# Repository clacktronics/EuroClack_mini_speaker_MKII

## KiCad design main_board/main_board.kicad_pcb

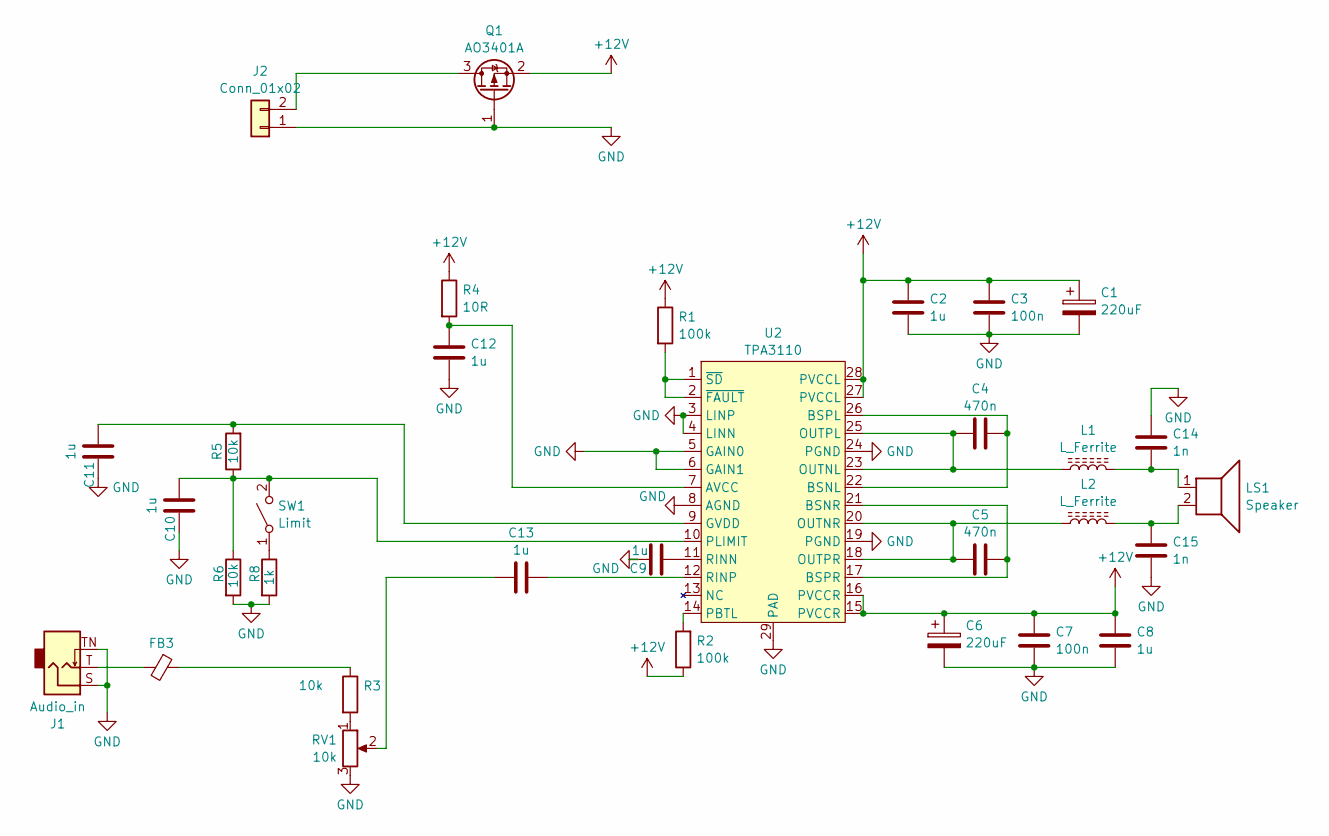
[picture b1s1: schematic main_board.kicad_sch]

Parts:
C1, C6: 220uF; CP_Elec_6.3x5.4; LCSC C2977551
C2, C8, C9, C10, C11, C12, C13: 1u; C_0805_2012Metric; LCSC C28323
C3, C7: 100n; C_0805_2012Metric; LCSC C28233
C4, C5: 470n; C_0805_2012Metric; LCSC C13967
C14, C15: 1n; C_0805_2012Metric; LCSC C46653
FB3: FerriteBead_Small; R_0603_1608Metric; LCSC C1002
J1: Audio_in; Jack_3.5mm_QingPu_WQP-PJ398SM_Vertical
J2: Conn_01x02; PinHeader_1x02_P2.54mm_Vertical
L1, L2: L_Ferrite; IND-SMD_L7.5-W7.5; LCSC C58313
LS1: Speaker; PinHeader_1x02_P2.54mm_Vertical
Q1: AO3401A; SOT-23-3; LCSC C15127
R1, R2: 100k; R_0603_1608Metric; LCSC C25803
R3, R5, R6: 10k; R_0603_1608Metric; LCSC C25804
R4: 10R; R_0805_2012Metric; LCSC C17415
R8: 1k; R_0603_1608Metric; LCSC C21190
RV1: 10k; POT_TH_Alps_RK09K_Single_Vertical
SW1: Limit; SW-SMD_SK-3293S; LCSC C466006
U2: TPA3110; HTSSOP-28-1EP_4.4x9.7mm_P0.65mm_EP2.85x5.4mm_ThermalVias; LCSC C30132

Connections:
+12V: C1.1, C2.1, C3.1, C6.1, C7.1, C8.1, Q1.2 (S), R1.1, R2.1, R4.1, U2.15 (PVCCR), U2.16 (PVCCR), U2.27 (PVCCL), U2.28 (PVCCL)
GND: C1.2, C2.2, C3.2, C6.2, C7.2, C8.2, C9.1, C10.1, C11.1, C12.1, C14.1, C15.2, J1.S, J1.TN, J2.1, Q1.1 (G), R6.2, R8.2, RV1.3, U2.3 (LINP), U2.4 (LINN), U2.5 (GAIN0), U2.6 (GAIN1), U2.8 (AGND), U2.19 (PGND), U2.24 (PGND), U2.29 (PAD)
unnamed: C13.2, RV1.2
unnamed: C14.2, L1.2, LS1.1
unnamed: C15.1, L2.2, LS1.2
unnamed: FB3.1, R3.1
unnamed: FB3.2, J1.T
unnamed: J2.2, Q1.3 (D)
unnamed: R3.2, RV1.1
unnamed: R8.1, SW1.1 (A)
unnamed: C10.2, R5.1, R6.1, SW1.2 (B), U2.10 (PLIMIT)
unnamed: C12.2, R4.2, U2.7 (AVCC)
unnamed: C4.2, U2.22 (BSNL), U2.26 (BSPL)
unnamed: C5.2, U2.17 (BSPR), U2.21 (BSNR)
unnamed: C11.2, R5.2, U2.9 (GVDD)
unnamed: C4.1, L1.1, U2.23 (OUTNL), U2.25 (OUTPL)
unnamed: C5.1, L2.1, U2.18 (OUTPR), U2.20 (OUTNR)
unnamed: R2.2, U2.14 (PBTL)
unnamed: C9.2, U2.11 (RINN)
unnamed: C13.1, U2.12 (RINP)
unnamed: R1.2, U2.1 (~SD), U2.2 (~FAULT)

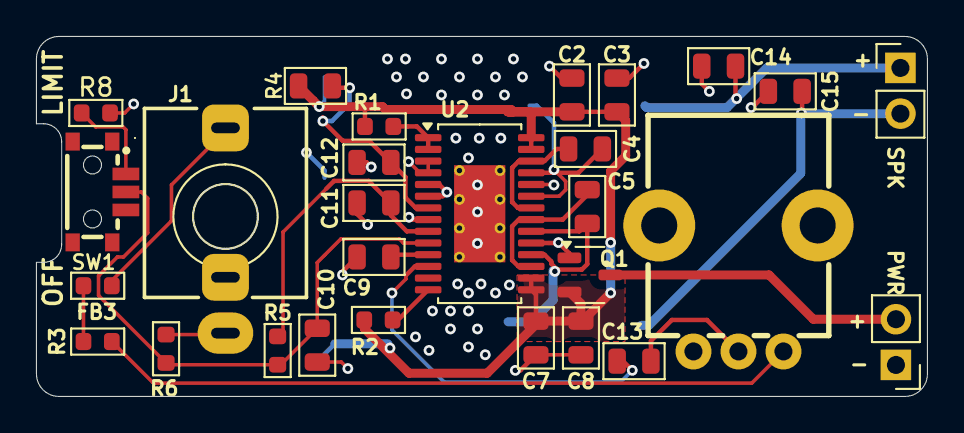
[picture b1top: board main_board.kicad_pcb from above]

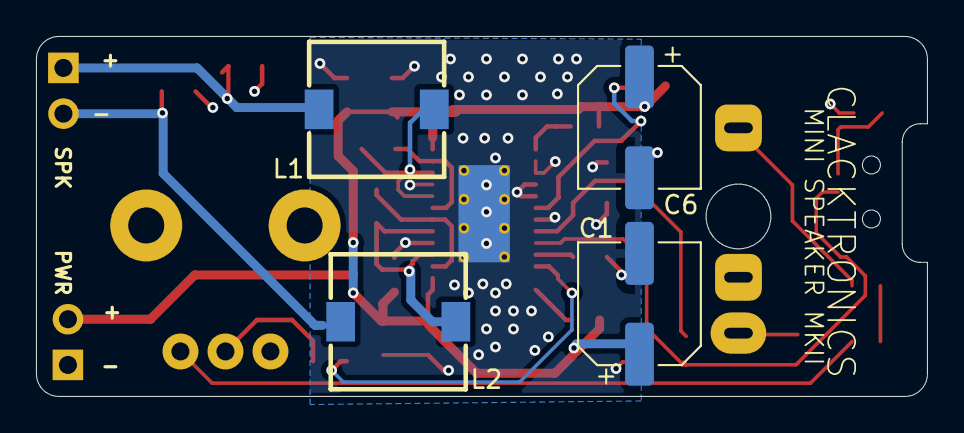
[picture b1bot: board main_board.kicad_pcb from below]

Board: 4 copper layers, 49.5 x 20.0 mm, 32 parts (4 on the bottom side), 21 nets.

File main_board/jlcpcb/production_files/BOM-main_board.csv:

Comment,Designator,Footprint,LCSC,Quantity
FerriteBead_Small,FB3,R_0603_1608Metric,C1002,1
470n,"C4,C5",C_0805_2012Metric,C13967,2
AO3401A,Q1,SOT-23-3,C15127,1
10R,R4,R_0805_2012Metric,C17415,1
1k,R8,R_0603_1608Metric,C21190,1
100k,"R1,R2",R_0603_1608Metric,C25803,2
10k,"R3,R5,R6",R_0603_1608Metric,C25804,3
100n,"C3,C7",C_0805_2012Metric,C28233,2
1u,"C10,C11,C12,C13,C2,C8,C9",C_0805_2012Metric,C28323,7
220uF,"C1,C6",CP_Elec_6.3x5.4,C2977551,2
TPA3110,U2,HTSSOP-28-1EP_4.4x9.7mm_P0.65mm_EP2.85x5.4mm_ThermalVias,C30132,1
Limit,SW1,SW-SMD_SK-3293S,C466006,1
1n,"C14,C15",C_0805_2012Metric,C46653,2
L_Ferrite,"L1,L2",IND-SMD_L7.5-W7.5,C58313,2
